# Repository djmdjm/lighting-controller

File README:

Some code for Atmel AVR MCUs that I find handy.

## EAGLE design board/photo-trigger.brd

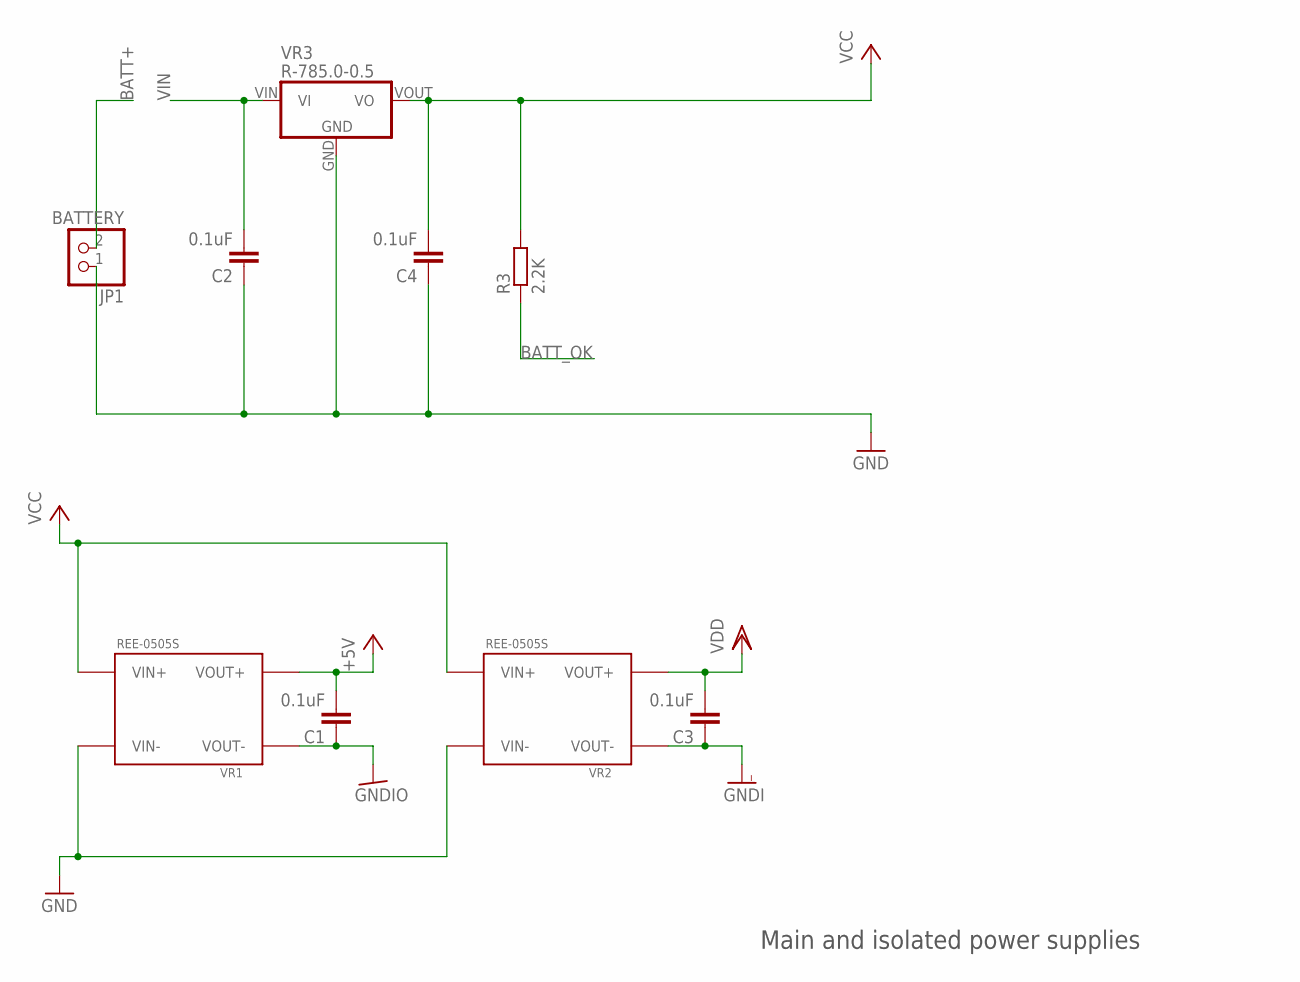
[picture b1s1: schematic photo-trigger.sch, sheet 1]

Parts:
C1, C2, C3, C4: 0.1uF; C050-035X075
JP1: BATTERY; 1X02
R3: 2.2K; 0207/10
VR1, VR2: REE-0505S; RECOM-REE
VR3: R-785.0-0.5; RECOM-R78

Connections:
+5V: C1.2, VR1.VOUT+; also elsewhere on the board
BATT+: JP1.2; also elsewhere on the board
BATT_OK: R3.1; also elsewhere on the board
GND: C2.1, C4.1, JP1.1, VR1.VIN-, VR2.VIN-, VR3.GND; also elsewhere on the board
GNDI: C3.1, VR2.VOUT-; also elsewhere on the board
GNDIO: C1.1, VR1.VOUT-; also elsewhere on the board
VCC: C4.2, R3.2, VR1.VIN+, VR2.VIN+, VR3.VOUT (VO); also elsewhere on the board
VDD: C3.2, VR2.VOUT+; also elsewhere on the board
VIN: C2.2, VR3.VIN (VI); also elsewhere on the board

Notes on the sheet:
Main and isolated power supplies

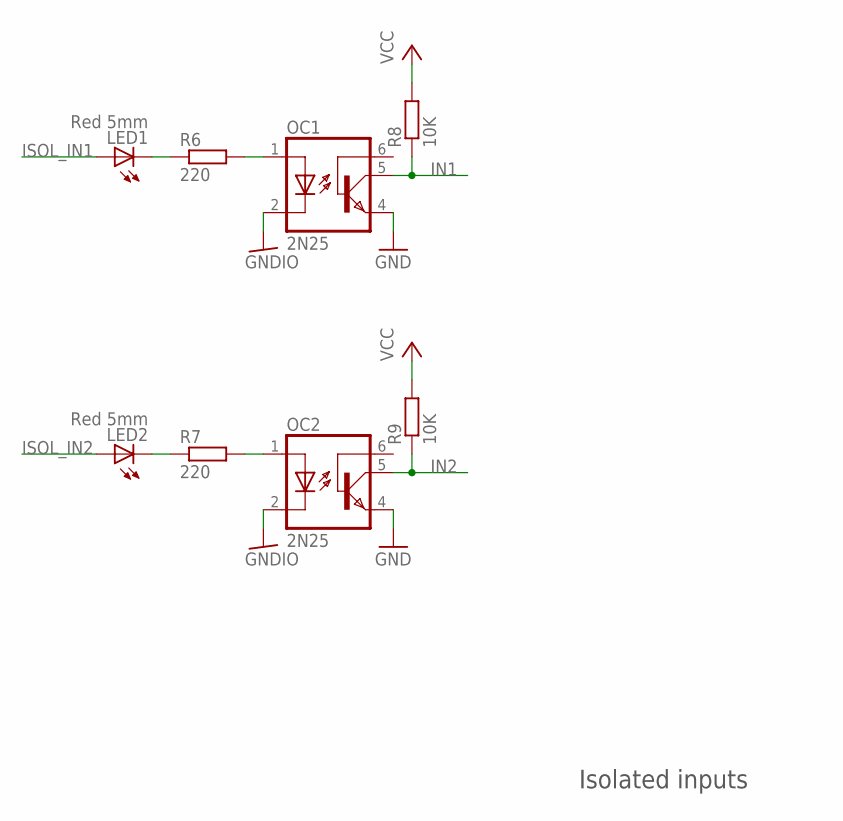
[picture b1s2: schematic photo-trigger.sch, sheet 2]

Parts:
LED1, LED2: Red 5mm; LED5MM
OC1, OC2: 2N25; DIL-06
R6, R7: 220; 0207/10
R8, R9: 10K; 0207/10

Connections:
GND: OC1.4 (EMI), OC2.4 (EMI); also elsewhere on the board
GNDIO: OC1.2 (C), OC2.2 (C); also elsewhere on the board
IN1: OC1.5 (COL), R8.1; also elsewhere on the board
IN2: OC2.5 (COL), R9.1; also elsewhere on the board
ISOL_IN1: LED1.A; also elsewhere on the board
ISOL_IN2: LED2.A; also elsewhere on the board
unnamed: OC1.1 (A), R6.2
unnamed: OC2.1 (A), R7.2
unnamed: LED2.K (C), R7.1
unnamed: LED1.K (C), R6.1
VCC: R8.2, R9.2; also elsewhere on the board

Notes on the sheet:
Isolated inputs

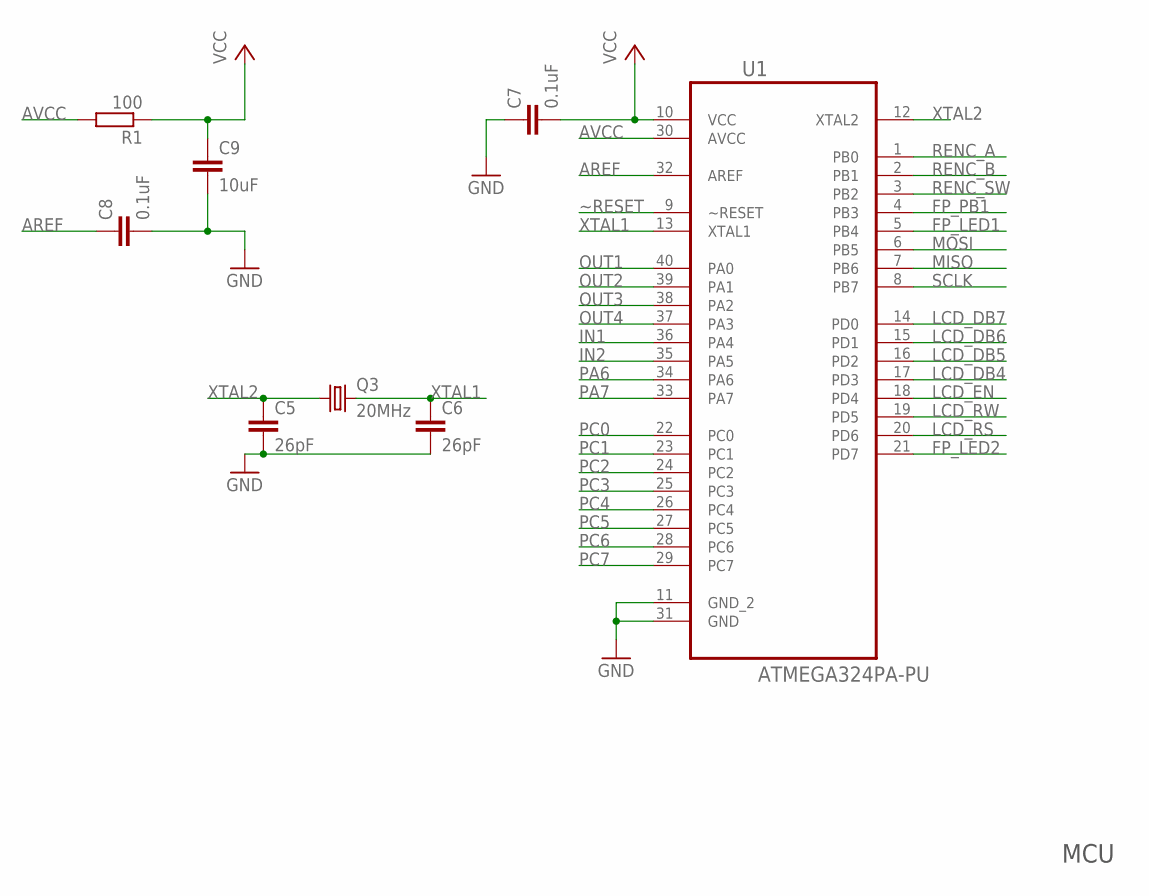
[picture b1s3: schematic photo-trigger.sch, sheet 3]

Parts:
C5, C6: 26pF; C025-025X050
C7, C8: 0.1uF; C050-035X075
C9: 10uF; C050-035X075
Q3: 20MHz; HC49/S
R1: 100; 0207/10
U1: ATMEGA324PA-PU; DIP254P1524X482-40

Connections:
AREF: C8.1, U1.32 (AREF)
AVCC: R1.2, U1.30 (AVCC)
FP_LED1: U1.5 (PB4); also elsewhere on the board
FP_LED2: U1.21 (PD7); also elsewhere on the board
FP_PB1: U1.4 (PB3); also elsewhere on the board
GND: C5.2, C6.2, C7.1, C8.2, C9.2, U1.11 (GND_2), U1.31 (GND); also elsewhere on the board
IN1: U1.36 (PA4); also elsewhere on the board
IN2: U1.35 (PA5); also elsewhere on the board
LCD_DB4: U1.17 (PD3); also elsewhere on the board
LCD_DB5: U1.16 (PD2); also elsewhere on the board
LCD_DB6: U1.15 (PD1); also elsewhere on the board
LCD_DB7: U1.14 (PD0); also elsewhere on the board
LCD_EN: U1.18 (PD4); also elsewhere on the board
LCD_RS: U1.20 (PD6); also elsewhere on the board
LCD_RW: U1.19 (PD5); also elsewhere on the board
MISO: U1.7 (PB6); also elsewhere on the board
MOSI: U1.6 (PB5); also elsewhere on the board
OUT1: U1.40 (PA0); also elsewhere on the board
OUT2: U1.39 (PA1); also elsewhere on the board
OUT3: U1.38 (PA2); also elsewhere on the board
OUT4: U1.37 (PA3); also elsewhere on the board
PA6: U1.34 (PA6); also elsewhere on the board
PA7: U1.33 (PA7); also elsewhere on the board
PC0: U1.22 (PC0); also elsewhere on the board
PC1: U1.23 (PC1); also elsewhere on the board
PC2: U1.24 (PC2); also elsewhere on the board
PC3: U1.25 (PC3); also elsewhere on the board
PC4: U1.26 (PC4); also elsewhere on the board
PC5: U1.27 (PC5); also elsewhere on the board
PC6: U1.28 (PC6); also elsewhere on the board
PC7: U1.29 (PC7); also elsewhere on the board
RENC_A: U1.1 (PB0); also elsewhere on the board
RENC_B: U1.2 (PB1); also elsewhere on the board
RENC_SW: U1.3 (PB2); also elsewhere on the board
SCLK: U1.8 (PB7); also elsewhere on the board
VCC: C7.2, C9.1, R1.1, U1.10 (VCC); also elsewhere on the board
XTAL1: C6.1, Q3.2, U1.13 (XTAL1)
XTAL2: C5.1, Q3.1, U1.12 (XTAL2)
~RESET: U1.9 (~RESET); also elsewhere on the board

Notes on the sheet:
MCU

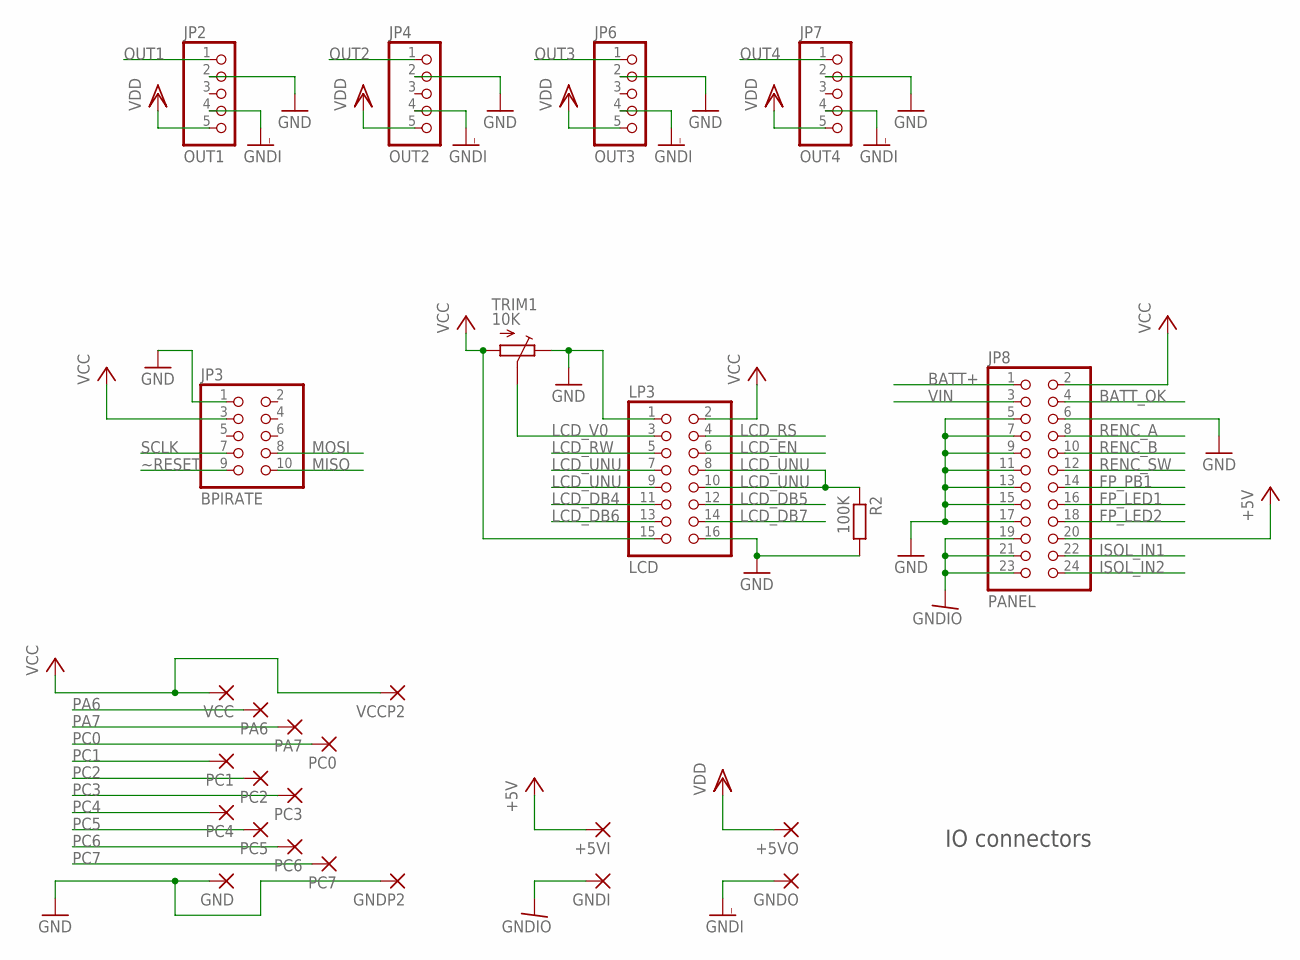
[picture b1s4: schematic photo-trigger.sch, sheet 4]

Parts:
+5VI: +5VI; PAD1.9/0.9
+5VO: +5VO; PAD1.9/0.9
GND: GND; PAD1.9/0.9
GNDI: GNDI; PAD1.9/0.9
GNDO: GNDO; PAD1.9/0.9
GNDP2: GND; PAD1.9/0.9
JP2: OUT1; 1X05
JP3: BPIRATE; 2X05
JP4: OUT2; 1X05
JP6: OUT3; 1X05
JP7: OUT4; 1X05
JP8: PANEL; 2X12
LP3: LCD; 2X08
PA6: PA2; PAD1.9/0.9
PA7: PA3; PAD1.9/0.9
PC0: PC0; PAD1.9/0.9
PC1: PC1; PAD1.9/0.9
PC2: PC2; PAD1.9/0.9
PC3: PC3; PAD1.9/0.9
PC4: PC4; PAD1.9/0.9
PC5: PC5; PAD1.9/0.9
PC6: PC6; PAD1.9/0.9
PC7: PC7; PAD1.9/0.9
R2: 100K; 0207/10
TRIM1: 10K; VISHAY-TRIM-63M-T607
VCC: VCC; PAD1.9/0.9
VCCP2: VCC; PAD1.9/0.9

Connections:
+5V: +5VI.P$1, JP8.20; also elsewhere on the board
BATT+: JP8.1; also elsewhere on the board
BATT_OK: JP8.4; also elsewhere on the board
FP_LED1: JP8.16; also elsewhere on the board
FP_LED2: JP8.18; also elsewhere on the board
FP_PB1: JP8.14; also elsewhere on the board
GND: GND.P$1, GNDP2.P$1, JP2.2, JP3.1, JP4.2, JP6.2, JP7.2, JP8.5, JP8.6, JP8.7, JP8.9, JP8.11, JP8.13, JP8.15, JP8.17, LP3.1, LP3.16, R2.2, TRIM1.P$3 (E); also elsewhere on the board
GNDI: GNDO.P$1, JP2.4, JP4.4, JP6.4, JP7.4; also elsewhere on the board
GNDIO: GNDI.P$1, JP8.19, JP8.21, JP8.23; also elsewhere on the board
ISOL_IN1: JP8.22; also elsewhere on the board
ISOL_IN2: JP8.24; also elsewhere on the board
LCD_DB4: LP3.11; also elsewhere on the board
LCD_DB5: LP3.12; also elsewhere on the board
LCD_DB6: LP3.13; also elsewhere on the board
LCD_DB7: LP3.14; also elsewhere on the board
LCD_EN: LP3.6; also elsewhere on the board
LCD_RS: LP3.4; also elsewhere on the board
LCD_RW: LP3.5; also elsewhere on the board
LCD_UNU: LP3.7, LP3.8, LP3.9, LP3.10, R2.1
LCD_V0: LP3.3, TRIM1.P$2 (S)
MISO: JP3.10; also elsewhere on the board
MOSI: JP3.8; also elsewhere on the board
OUT1: JP2.1; also elsewhere on the board
OUT2: JP4.1; also elsewhere on the board
OUT3: JP6.1; also elsewhere on the board
OUT4: JP7.1; also elsewhere on the board
PA6: PA6.P$1; also elsewhere on the board
PA7: PA7.P$1; also elsewhere on the board
PC0: PC0.P$1; also elsewhere on the board
PC1: PC1.P$1; also elsewhere on the board
PC2: PC2.P$1; also elsewhere on the board
PC3: PC3.P$1; also elsewhere on the board
PC4: PC4.P$1; also elsewhere on the board
PC5: PC5.P$1; also elsewhere on the board
PC6: PC6.P$1; also elsewhere on the board
PC7: PC7.P$1; also elsewhere on the board
RENC_A: JP8.8; also elsewhere on the board
RENC_B: JP8.10; also elsewhere on the board
RENC_SW: JP8.12; also elsewhere on the board
SCLK: JP3.7; also elsewhere on the board
VCC: JP3.3, JP8.2, LP3.2, LP3.15, TRIM1.P$1 (A), VCC.P$1, VCCP2.P$1; also elsewhere on the board
VDD: +5VO.P$1, JP2.5, JP4.5, JP6.5, JP7.5; also elsewhere on the board
VIN: JP8.3; also elsewhere on the board
~RESET: JP3.9; also elsewhere on the board

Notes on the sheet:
IO connectors

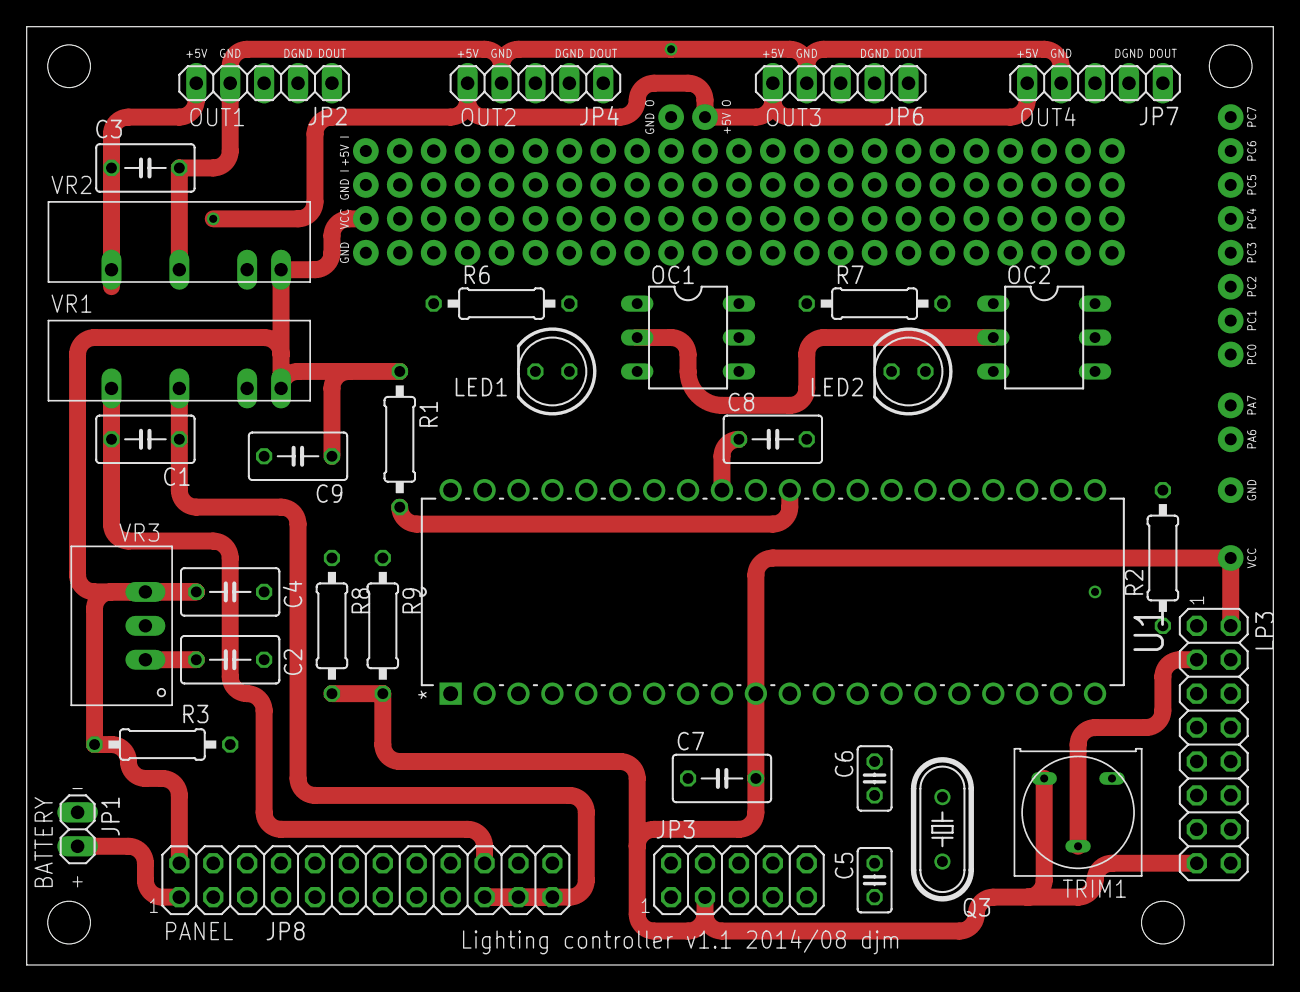
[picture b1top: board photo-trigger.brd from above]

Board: 4 copper layers, 93.4 x 70.3 mm, 52 parts (0 on the bottom side), 54 nets.

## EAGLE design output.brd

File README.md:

Photographic Lighting Timer
===========================

This is a small lighting controller circuit based around an AVR
microcontroller. It supports two inputs and two outputs and
configurable timing delays. The outputs use MOSFETs that should
be good for up to 50VDC and 20A.

The `board/` directory contains the Eagle files for the board and
`firmware/` contains the source for the firmware. You'll need
avr-gcc et al. to build it. `make load` will attempt to program
the firmware using my setup (avrdude w/ buspirate on
`/dev/cuaU1`).

NB. the current version of the board has not been built and the
old version that I did build had some problems that required a
bit of rework. I beat the old version into working shape and that
was good enough for my immediate needs.

Not included in the schematics are the front-panel controls: a
power toggle, momentary switch, generic rotary encoder (w/ press
switch) and 4x20 HD44870-style LCD. The switches and encoder need
pull-ups and debouncing caps.

The firmware allows triggering from logical combinations of the
inputs (e.g. "input 1 high and input 2 low"). Upon triggering it
waits a configurable delay (from 1us to ~1ksec) and enables one
or both outputs for a configurable duration. It also supports a
strobe mode that goes from milli-hertz to close to 1MHz frequency
and has adjustable duration and duty cycle.

The outputs are not isolated from each other, but they are
isolated from the inputs and the main board. Likewise the inputs
are isolated from the main board and the output but not from each
other.

This was only my 2nd attempt at cutting a board, so it's probably
terrible. You have been warned :)

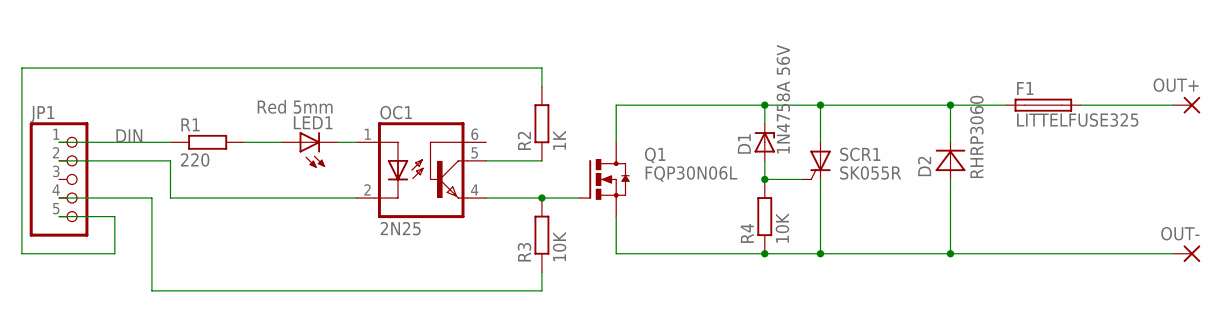
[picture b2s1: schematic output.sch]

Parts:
D1: 1N4758A 56V; DO41Z10
D2: RHRP3060; TO-220CAS-HS
F1: LITTELFUSE325; LITTELFUSE-325
JP1: PINHD-1X5; 1X05
LED1: Red 5mm; LED5MM
OC1: 2N25; DIL-06
OUT+: 2,54/1,1
OUT-: 2,54/1,1
Q1: FQP30N06L; TO-220BV-HS
R1: 220; 0207/10
R2: 1K; 0207/10
R3, R4: 10K; 0207/10
SCR1: SK055R; TO-220V-HS

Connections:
DGND: JP1.2, OC1.2 (C)
DIN: JP1.1, R1.1
ISOL_GND: JP1.4, R3.1
ISOL_OUT+: D1.C, D2.C, F1.P$1 (1), Q1.D, SCR1.2 (A)
ISOL_OUT-: D2.A, OUT-.1, Q1.S, R4.1, SCR1.1 (C)
ISOL_VDD: JP1.5, R2.2
unnamed: D1.A, R4.2, SCR1.3 (G)
unnamed: OC1.5 (COL), R2.1
unnamed: OC1.4 (EMI), Q1.G, R3.2
unnamed: LED1.K (C), OC1.1 (A)
unnamed: LED1.A, R1.2
unnamed: F1.P$2 (2), OUT+.1

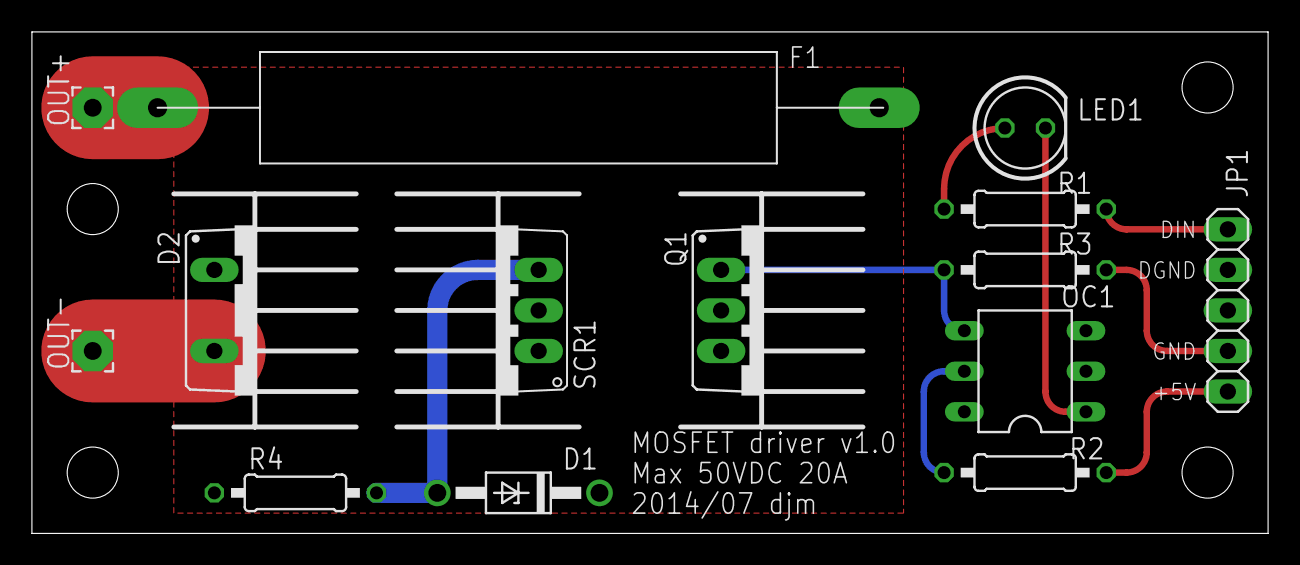
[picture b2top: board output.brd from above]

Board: 2 copper layers, 77.5 x 31.4 mm, 14 parts (0 on the bottom side), 12 nets.

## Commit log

2013-10-25 initial import of AVR code that I'm playing with
2013-10-27 add basic SPI convenience routines and a tiny AD56x8 driver; just enough to setup the chip and get it to do conversions.
2013-10-30 move the SS of my AD5688 to PORTE to free up an interruptable PORTB pin for some other stuff.
2013-10-30 we don't use SS in the SPI API, so nuke it entirely
2013-10-30 Simple event queue API. Implemented as ring buffer with a simple priority system (non-important messages are dropped when the ring is full, important messages clobber existing messages on the ring)
2013-10-30 driver for common two-wire quadrature rotary encoders, using interrupts.
2013-10-30 more more stuff to better use available (and diminishing!) pins
2013-10-30 option for hex conversion to prepend '0x' rjustify() function to right-justify text
2013-10-30 add recently added code, better compile options
2013-10-30 update lamp-test app
2013-11-21 support SPI devices that sample on the leading edge of SCLK
    setup SS line; apparently if it is configured as an input it will
    put the AVR into SPI slave mode automatically!
2013-11-21 clock phase and SS handline
2013-11-21 move the interrupt logic into its own function and make the setup of the handler optional, for cases where we need to tie it in with other handlers
2013-11-21 WIP MCP23S1[78] 16-pin SPI I/O multiplexer driver; still with loads of debug/tryout gunk included
2013-11-21 messing around
2013-11-21 add MCP23S1x driver
2013-11-28 allow control, data and enable signals to live on different ports
2013-11-28 working on a Teensy 2.0 now; change MCU type
2013-11-28 working MCP23S1X driver; enough to setup, control I/O direction and read/write pins.
2013-11-28 starting to look like a three-channel analog sequencer
2013-11-28 Rename and describe
2013-11-28 add to do file
2014-07-28 import my EAGLE files
2014-07-30 correct device name to match library
2014-07-30 correct diode lead order in part/package name
    MUR860 and RHRP3060 have pin 1 as cathode and pin 2 as anode,
    so s/TO-220AC/TO-220CA/ to avoid confusion.
2014-08-11 fix DAC output setting
2014-08-11 add support for interrupts and input bit flipping
2014-08-11 working prototype of digital side of sequencer
    runs fixed output sequence continually
2014-08-11 rework event queue a little
    events now contain 3 x uint8 values (enough for our MIDI needs)
2014-08-11 simple MIDI receiver implementation
    handles a small, receive-only MIDI subseq. Plumbs received MIDI
    messages into the event queue.
2014-08-11 breadboard prototype configuration/test harness
    MIDI->CV and CV sequencer
2014-08-15 revised after building v1.0 boards; lots of fixes
    ripped out power status indicator circuit - it didn't work.
    replaced with a simple power LED.
    fixed footprint problem for Recom REE isolated VRMs
    rewired LCD socket to be easier to handle at the LCD end
    fixed MCU AREF and AGND
    expanded prototype area; embiggened pads to make them easier to
2014-08-15 few more layout tweaks; embiggen more wirepads
2014-08-15 v2.1 to pull in updated footprints
    embiggened drills and pads
2014-08-15 move drills to avoid heatsinks
2014-10-25 multiple improvements
    add lcd_clear_eol(), lcd_chars(), lcd_char(), lcd_fill() functions
    add support for four-row displays
    add support for programming custom characters
2014-10-25 syntax error
2014-10-25 WIP UI for lighting controller box
2014-10-29 handle long integers
2014-10-29 add event_drain() and event_sleep()
    event_drain() drains all events from the queue.
    event_sleep() enters one of the AVR sleep modes until
    an interrupt generates an event.
2014-10-29 interrupt control methods and a bit of debouncing
    Added encoder_interrupt_enable() and encoder_interrupt_disable()
    Added a 50us delay to the interrupt handler to allow input to
    settle.
2014-10-29 add EV_BUTTON event for button presses
2014-10-29 Final (?) code for lighting controller
    Added user-interface with multiple editable fields
    Added delay code for oneshot and strobe modes
    Seems to work...
2014-10-29 Separate project for lighting controller
    (branched/matriculated from avr-playground)
2014-10-29 prune for inclusion in separate project
2014-10-29 add README
2014-10-29 gratuitous change to test mirroring
